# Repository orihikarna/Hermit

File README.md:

# Hermit - An Ergonomic Narrow-Pitch Split Keyboard

</img>

## Introduction
This is a personal hobby project on DIY keyboard.
The name *Hermit* comes from its key switch layout: it looked like a hermit crab.

Before working on this "full" keyboard, I made a test split keypad with 10 keys as a proof of concept model, which was named *Zoea*.

</img>

### Features
- Symmetric split with 60 keys
  - Key switch: Choc V2
  - Narrow pitch: 17.4 x 16.8mm
  - Thumb keys placed a bit further (to press them with the first joint)
  - Full color RGB LED
- Controller
  - ARM (STM32F042K6T6)
  - I/O expander (MCP23017) via I2C (using USB Type-C cable)
  - Debounce RC circuit (firmware reads Col 1ms after writing Row)
- Firmware
  - C++ bare-metal (STM32CubeIDE)
  - Stream processing with FIFO's (no immediate sending of key presses/releases)
  - Emacs translation (ex. `C-d` -> `Del`)

## Key switch layout
Before assembling ErgoDash, I really liked the key touch of Realforce and had used it for a decade.
However, once I got used to ErgoDash, I could not go back to Realforce anymore because `B` key was too far for my left index finger.
In fact, I started feeling pain in the index finger after typing on Realforce for a day.

One day, I came across [Treadstone](https://booth.pm/ja/items/1434972) layout, where the `B` key, or the left half of the bottom row, is shifted to the left a bit.
I thought this is the answer for me and I should follow this design.

### Cardboard prototyping
To begin with, I placed keycaps on a cardboard with lines of double sided tapes on it, and try tapping on it.
Sometimes added more keys, and other times removed some of them to find one that suits my fingers.

</img>

### 3D printer prototyping
After I purchased a 3D printer, I continued the seek for the layout using the actual Choc V2 key switches on 3D printed frames.
It enabled me to more finely adjust:
- Number of keys
- Key pitch: 17.0 ~ 18.0mm
- Key column positions and angles, especially for the thumbs

I usually use Japanese key layouts, and I found that 60 keys is the minimum that I can accept.
I wanted to keep most of the symbol keys on the board (without layers).

</img>

### Parametric model
When the layout was roughly determined, I tried to parametrize the layout to adjust the degree of ergonomic-ness.
The strategies are:
- Ring finger keys are on a straight line
- `B` is a bit on the left of `G`
- Pinky finger keys are lower than ring finger keys
- Keys are tightly touching to each other

And finally settled down on the current layout.

</img>

## PCB Design
This keyboard is composed of 6 PCB layers and is 8mm thick in total.
- Top layer (1.6mm)
- Second top layer (0.8mm)
- Circuit layer (1.6mm, Left and Right)
- Mid layer (1.2mm x2)
- Bottom layer (1.6mm)

</img>

I used KiCad v5.1.5 for the PCB design.

### Top
- Supports key switches.
- Common to Left and Right (reversible).

</img>

### Second top
- Fills in the gap between the top plate and the bottom of the box part of the key switches.
- Gives holes for USB connecter terminals.
- Common to Left and Right.

</img>

#### Circuit Left & Right
- Implements the circuitry, and USB connecters.

</img>
</img>

#### Middle
- Fills in the gap between the bottom plate and the bottom of the axis part of the key switches.
- USB connecter island will be removed for Left.

</img>

#### Bottom
- Common to Left and Right.

</img>

### Place & route by Python script
All the footprint placement, wire routing, vias, silkscreen labels, Edge.Cuts and GND zones are done by a Python script.

Currently, only the component side (Front or Back) needs to be set manually first.
Then, from `Script Console` of Pcbnew layout editor, run
```
exec(open('/(your path)/Hermit/python/place-route-Hermit.py').read())
```
and everything will be done in seconds!
(Although it took 2 month for me to write the script, of course!)

For example, in the script, the wire from C21 (debounce capacitor) pad 1 to U1 (main mcu) pad 29 is written as:
```
            ('C21', '1', 'U1', '29', w_mcu, (Dird, 90, ([(5.8, 90)], 0), r_col)),
```
This means that:
- the wire width is w_mcu
- from C21 pad 1, extend wire in the direction of 90deg
- from U1 pad 29, draw a wire for 5.8mm in the 90deg direction, and then, extend it to the direction of 0deg
- the intersection of the two lines will automatically be found
- make corners round by radius r_col

</img>

This way, the wiring is parallel to each part and looks roundy at corners.

## Debounce RC circuit
The mechanical key switches chatter sometimes.
Most DIY keyboards use software debouncing technique that comes with qmk (the standard keyboard firmware), where the key state (pressed or not) is examined twice with several milliseconds interval.
So, the switch bounce is hidden usually.
However, for the last two years, I experienced a couple of keys of my ErgoDash exhibited the chattering only in a specific season, i.e., in July or August in Japan.
I guess the software debounce might not be enough when it is very hot and super humid.
I've therefore added debounce RC for each column lines:

</img>

- When a key switch is released,
  - the Col lines are pulled down to GND.
  - the capacitors are fully charged.
- When a key switch is pressed,
  - the Row lines discharge the capacitors through key matrix diodes.
  - the Col lines rise to 5.0V or 3.3V minus 0.7V of the diode drop
- The time constant is different for discharging and charging, but they are set to about 1ms.
- Firmware needs to wait for 1~2ms before reading Col lines after writing Row lines.

I will check if this will actually contribute to reduce the switch bounce in the next summer!

For more information on hardware debounce, please refer to articles such as
[Ultimate Guide to Switch Debounce (Part 3)](https://www.eejournal.com/article/ultimate-guide-to-switch-debounce-part-3/)

## Rectangular holes for hexagon spacers
In Zoea PCB, it was useful to use hexagonal hole for spacers to keep them fixed: they won't rotate when tightening screws from the top and the bottom plates.
However, I needed to carefully choose the hexagon radius and the radius of the hexagon corners taking into account the endmill diameter.
So, this time, I used rectangular holes for the same purpose. I didn't have to consider much about the radius of the rectangle corners because any value would be fine with hexagon.

</img>

## Boundary avoidance using distance transform
I wanted to fill the surface of the top and the bottom plates with some design other than just nothing.
I'm not an artsy person at all, so I decided to draw simple stripes on them that curve along with the key switch angles.
The problem was that, how to end the stripe lines at the boundary of the board, screw holes, and of course the key switch holes. I didn't want that to happen all of a sudden abruptly.

So, I figured out a way to end lines just before the boundaries:
1. Export Edge.Cuts to svg (KiCad)
1. Rasterize svg to png (cairosvg Python package)
1. Binarize png to a mask image
1. Find connected components in the mask (OpenCV)
1. Choose the PCB component
1. Set initial distance (inside PCB = infinity, outside = 0)
1. Execute distance transform (OpenCV)

Then, you will get the distance from the boundaries.
It would be easier to end lines nicely at the boundaries: if it is near the boundary, you can use the distance value to find where to end the line.

The following figures are from Zoea top layer. First, the distance transform.

</img>

The final stripes on PCB. The thickness is reversed on its front and back.

</img>

It looked ok that time, however, I wanted to get closer to the edge this time...
So, divided thick lines into a multiple of thin lines:

</img>

and then, drew vertical / slant lines that connect the ends of thin horizontal lines:

</img>

## Firmware
For my studying of embedded programming, I wrote the firmware from scratch instead of using qmk.

### Stream processing
One thing I was thinking about qmk was register_code() and unregister_code() functions: these are used everywhere to send keycodes in the chain of processing.
However, since they send keycodes immediately, there is no room to to do more processing on the processed keycodes in the middle of the chain.

Of course, there are pros and cons.
But I wanted to try a stream structure, where each keycode processor is connected with FIFOs one after another to allow for successive processing.
Also, only one HID report will be prepared in the big loop that runs every 2ms.

A difficult part is the estimation of the required size for each FIFO.
If the FIFO size is too short, a processor in the chain cannot output anything and the entire stream would get stuck.

### Full Color RGB LED
At first, I placed LC8822-2020 on the key switch side of PCB.
They are good since they have separate data and clock lines (total 6 lines).
However, I noticed later that when they got broken, it is difficult to replace them because key switches are soldered above them.

Then, I decided to use SK6812-MINI-E, which is commonly used in DIY keyboards.
It has only one line for both data and clock, so it needs strict timing to send data.
There are 60 keys on Hermit, so that it takes 2ms to send series of data for all of them at once.
As 2ms felt too long, I split them to left and right half, and reduced the duration of interrupt-disabled periods to 1ms each.

</img>

### Emacs translation
I have been using Emacs key-binding for years.
There are ways to emulate it in a software manner on Windows, but what if it is inside a keyboard itself?

Although the current implementation needs tap & hold for single press of CTRL and ALT, other than that, it is working nicely!

### Minimizing the code size
At first, the code bloated with STM32 HAL USB library and printf (for debugging purpose) to more than 20KB.
However, thanks to STM32 LL library and the following libraries:
- [libusb_stm32](https://github.com/dmitrystu/libusb_stm32)
- [mini-printf](https://github.com/mludvig/mini-printf)

even after implemented RGB effects and Emacs translations, the current code size is:
- text: 16KB
- data+bss: 2.5KB

namely, only the half of STM32F042 capacity (32KB/6KB) is used.

## USB connector holders
For USB Type-C connectors, I gave up using the full 24-pin type due to the lack of my ability to solder them on PCB.
Instead, 16-pin type is used, where I2C is sent over D+/D- and LED signal is sent over SBU1/2.
Although other USB3.0 signal lines are not used at all, only because SBU1/2 is used, "full spec" Type-C cable is required to connect left and right.
They are thick in general and their stiffness gives strong forces on USB connectors.
So, I printed a simple-extrusion-work cable connector holder for them.
They need to be printed for each connector shape, but fit well and the cables are firmly attached to the keyboard.

</img>

## Finally, a short video
[Rainbow shaped Rainbow effect](https://twitter.com/orihikarna/status/1439446049446264836)

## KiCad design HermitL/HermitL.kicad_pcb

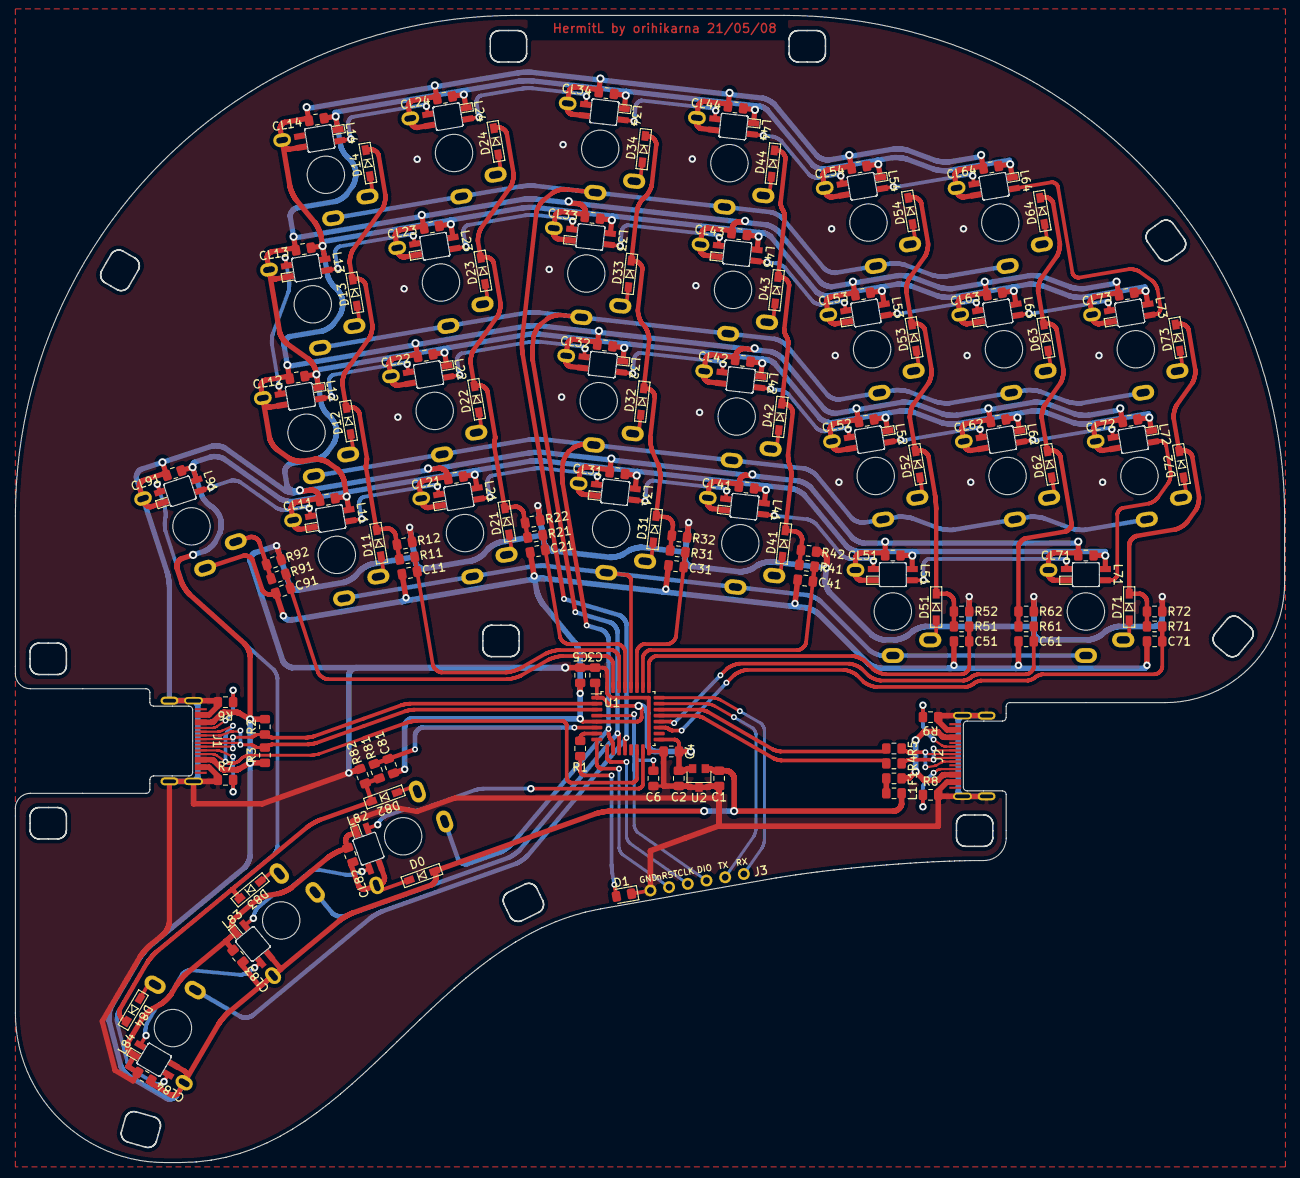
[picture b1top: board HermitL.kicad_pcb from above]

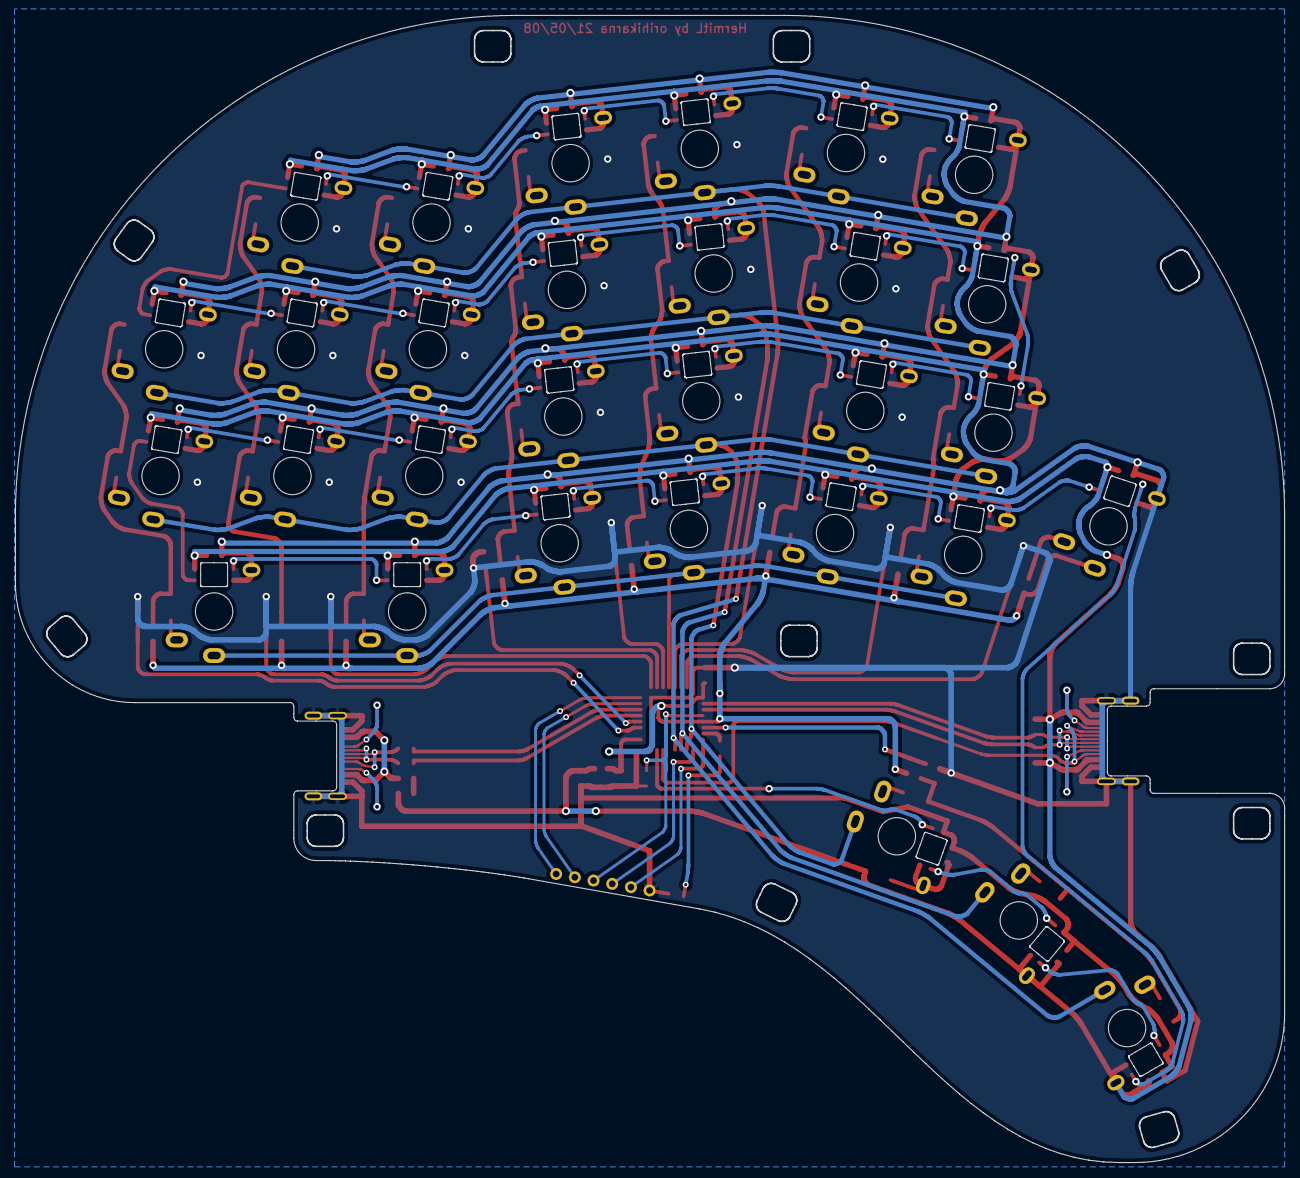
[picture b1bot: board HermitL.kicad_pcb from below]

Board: 2 copper layers, 169.9 x 153.6 mm, 170 parts (60 on the bottom side), 106 nets.

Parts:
C1: 1uF; C_0805_2012Metric_Pad1.15x1.40mm_HandSolder
C2: 10uF; C_0805_2012Metric_Pad1.15x1.40mm_HandSolder
C3, C4, C6: 0.1uF; C_0805_2012Metric_Pad1.15x1.40mm_HandSolder
C5: 4.7uF; C_0805_2012Metric_Pad1.15x1.40mm_HandSolder
C11, C21, C31, C41, C51, C61, C71, C81, C91: 33n; C_0805_2012Metric_Pad1.15x1.40mm_HandSolder
CL11, CL12, CL13, CL14, CL21, CL22, CL23, CL24, CL31, CL32, CL33, CL34, CL41, CL42, CL43, CL44, CL51, CL52, CL53, CL54, CL62, CL63, CL64, CL71, CL72, CL73, CL82, CL83, CL84, CL91: 0.1uF; C_0805_2012Metric_Pad1.15x1.40mm_HandSolder
D0, D11, D12, D13, D14, D21, D22, D23, D24, D31, D32, D33, D34, D41, D42, D43, D44, D51, D52, D53, D54, D62, D63, D64, D71, D72, D73, D82, D83, D84: D_Small; D_SMD
D1: LED; D_0805_2012Metric_Pad1.15x1.40mm_HandSolder
F1: Polyfuse; Fuse_0805_2012Metric_Pad1.15x1.40mm_HandSolder
J1, J2: USB_C_Receptacle_USB2.0; USB_C_Receptacle_Hirose_CX90M-16P
J3: Conn_01x06; PinHeader_1x06_P2.54mm_Vertical
L1: BLM21; L_0805_2012Metric_Pad1.15x1.40mm_HandSolder
L11, L12, L13, L14, L21, L22, L23, L24, L31, L32, L33, L34, L41, L42, L43, L44, L51, L52, L53, L54, L62, L63, L64, L71, L72, L73, L82, L83, L84, L91: SK6812-MINI-E
R1: 330; R_0805_2012Metric_Pad1.15x1.40mm_HandSolder
R2, R3: 2K2; R_0805_2012Metric_Pad1.15x1.40mm_HandSolder
R4, R5: 22; R_0805_2012Metric_Pad1.15x1.40mm_HandSolder
R6, R7, R8, R9: 5k1; R_0805_2012Metric_Pad1.15x1.40mm_HandSolder
R11, R21, R31, R41, R51, R61, R71, R81, R91: 10k; R_0805_2012Metric_Pad1.15x1.40mm_HandSolder
R12, R22, R32, R42, R52, R62, R72, R82, R92: 4k7; R_0805_2012Metric_Pad1.15x1.40mm_HandSolder
SW11, SW12, SW13, SW14, SW21, SW22, SW23, SW24, SW31, SW32, SW33, SW34, SW41, SW42, SW43, SW44, SW51, SW52, SW53, SW54, SW62, SW63, SW64, SW71, SW72, SW73, SW82, SW83, SW84, SW91: SW_ChocV2; ChocV2
U1: STM32F042K6Tx; LQFP-32_7x7mm_P0.8mm
U2: AP7333

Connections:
4V3: CL82.1, D0.1, L82.1, SW82.3
5V: C1.1, CL11.1, CL12.1, CL13.1, CL14.1, CL21.1, CL22.1, CL23.1, CL24.1, CL31.1, CL32.1, CL33.1, CL34.1, CL41.1, CL42.1, CL43.1, CL44.1, CL51.1, CL52.1, CL53.1, CL54.1, CL62.1, CL63.1, CL64.1, CL71.1, CL72.1, CL73.1, CL83.1, CL84.1, CL91.1, D0.2, J1.A4, J1.B4, L1.1, L11.1, L12.1, L13.1, L14.1, L21.1, L22.1, L23.1, L24.1, L31.1, L32.1, L33.1, L34.1, L41.1, L42.1, L43.1, L44.1, L51.1, L52.1, L53.1, L54.1, L62.1, L63.1, L64.1, L71.1, L72.1, L73.1, L83.1, L84.1, L91.1, R2.2, R3.2, SW12.3, SW14.3, SW22.3, SW24.3, SW32.3, SW34.3, SW42.3, SW44.3, SW52.3, SW54.3, SW62.3, SW64.3, SW72.3, SW83.3, SW84.3, U2.1
BOOT0: C91.1, R91.1, U1.31
COL1: C11.1, R11.1, U1.30
COL2: C21.1, R21.1, U1.29
COL3: C31.1, R31.1, U1.27
COL4: C41.1, R41.1, U1.26
COL5: C51.1, R51.1, U1.25
COL6: C61.1, R61.1, U1.20
COL7: C71.1, R71.1, U1.19
COL8: C81.1, R81.1, U1.6
DM: R4.2, U1.21
DP: R5.2, U1.22
GND: C1.2, C2.2, C3.2, C4.2, C5.2, C6.2, D1.1, J1.A1, J1.B1, J1.S1, J1.S2, J1.S3, J1.S4, J2.A1, J2.B1, J2.S1, J2.S2, J2.S3, J2.S4, J3.1, R6.2, R7.2, R8.2, R9.2, R12.1, R22.1, R32.1, R42.1, R52.1, R62.1, R72.1, R82.1, R92.1, U1.16, U1.32, U2.3
GNDD: CL11.2, CL12.2, CL13.2, CL14.2, CL21.2, CL22.2, CL23.2, CL24.2, CL31.2, CL32.2, CL33.2, CL34.2, CL41.2, CL42.2, CL43.2, CL44.2, CL51.2, CL52.2, CL53.2, CL54.2, CL62.2, CL63.2, CL64.2, CL71.2, CL72.2, CL73.2, CL82.2, CL83.2, CL84.2, CL91.2, L11.3, L12.3, L13.3, L14.3, L21.3, L22.3, L23.3, L24.3, L31.3, L32.3, L33.3, L34.3, L41.3, L42.3, L43.3, L44.3, L51.3, L52.3, L53.3, L54.3, L62.3, L63.3, L64.3, L71.3, L72.3, L73.3, L82.3, L83.3, L84.3, L91.3, SW11.3, SW13.3, SW21.3, SW23.3, SW31.3, SW33.3, SW41.3, SW43.3, SW51.3, SW53.3, SW63.3, SW71.3, SW73.3, SW91.3
LDI: L82.4, U1.15
LED: R1.1, U1.7
NRST: C6.1, J3.4, U1.4
unnamed: D1.2, R1.2
unnamed: D11.1, D12.1, D13.1, D14.1, R11.2, R12.2
unnamed: D11.2, SW11.2
unnamed: D12.2, SW12.2
unnamed: D13.2, SW13.2
unnamed: D14.2, SW14.2
unnamed: D21.1, D22.1, D23.1, D24.1, R21.2, R22.2
unnamed: D21.2, SW21.2
unnamed: D22.2, SW22.2
unnamed: D23.2, SW23.2
unnamed: D24.2, SW24.2
unnamed: D31.1, D32.1, D33.1, D34.1, R31.2, R32.2
unnamed: D31.2, SW31.2
unnamed: D32.2, SW32.2
unnamed: D33.2, SW33.2
unnamed: D34.2, SW34.2
unnamed: D41.1, D42.1, D43.1, D44.1, R41.2, R42.2
unnamed: D41.2, SW41.2
unnamed: D42.2, SW42.2
unnamed: D43.2, SW43.2
unnamed: D44.2, SW44.2
unnamed: D51.1, D52.1, D53.1, D54.1, R51.2, R52.2
unnamed: D51.2, SW51.2
unnamed: D52.2, SW52.2
unnamed: D53.2, SW53.2
unnamed: D54.2, SW54.2
unnamed: D62.1, D63.1, D64.1, R61.2, R62.2
unnamed: D62.2, SW62.2
unnamed: D63.2, SW63.2
unnamed: D64.2, SW64.2
unnamed: D71.1, D72.1, D73.1, R71.2, R72.2
unnamed: D71.2, SW71.2
unnamed: D72.2, SW72.2
unnamed: D73.2, SW73.2
unnamed: D82.1, D83.1, D84.1, R81.2, R82.2
unnamed: D82.2, SW82.2
unnamed: D83.2, SW83.2
unnamed: D84.2, SW84.2
unnamed: F1.2, L1.2
unnamed: J1.A5, R6.1
unnamed: J1.B5, R7.1
unnamed: J2.A5, R8.1
unnamed: J2.A6, J2.B6, R5.1
unnamed: J2.A7, J2.B7, R4.1
unnamed: J2.B5, R9.1
unnamed: L11.2, L21.4
unnamed: L11.4, L91.2
unnamed: L12.2, L13.4
unnamed: L12.4, L22.2
unnamed: L13.2, L23.4
unnamed: L14.4, L24.2
unnamed: L21.2, L31.4
unnamed: L22.4, L32.2
unnamed: L23.2, L33.4
unnamed: L24.4, L34.2
unnamed: L31.2, L41.4
unnamed: L32.4, L42.2
unnamed: L33.2, L43.4
unnamed: L34.4, L44.2
unnamed: L41.2, L51.4
unnamed: L42.4, L52.2
unnamed: L43.2, L53.4
unnamed: L44.4, L54.2
unnamed: L51.2, L71.4
unnamed: L52.4, L62.2
unnamed: L53.2, L63.4
unnamed: L54.4, L64.2
unnamed: L62.4, L72.2
unnamed: L63.2, L73.4
unnamed: L64.4, L73.2
unnamed: L71.2, L72.4
unnamed: L82.2, L83.4
unnamed: L83.2, L84.4
unnamed: L84.2, L91.4
unnamed: R91.2, R92.2, SW91.2
RDI: J1.A8, J1.B8, U1.14
ROW1: SW11.1, SW21.1, SW31.1, SW41.1, SW51.1, SW71.1, U1.28
ROW2: SW12.1, SW22.1, SW32.1, SW42.1, SW52.1, SW62.1, SW72.1, SW82.1, U1.10
ROW3: SW13.1, SW23.1, SW33.1, SW43.1, SW53.1, SW63.1, SW73.1, SW83.1, U1.11
ROW4: SW14.1, SW24.1, SW34.1, SW44.1, SW54.1, SW64.1, SW84.1, U1.12
RX: J3.3, U1.9
SCL: J1.A6, J1.B6, R3.1, U1.3
SDA: J1.A7, J1.B7, R2.1, U1.2
SWCLK: J3.6, U1.24
SWDIO: J3.5, U1.23
TX: J3.2, U1.8
VBUS: F1.1, J2.A4, J2.B4
VCC: C2.1, C3.1, C4.1, C5.1, C11.2, C21.2, C31.2, C41.2, C51.2, C61.2, C71.2, C81.2, C91.2, SW91.1, U1.1, U1.5, U1.17, U2.2

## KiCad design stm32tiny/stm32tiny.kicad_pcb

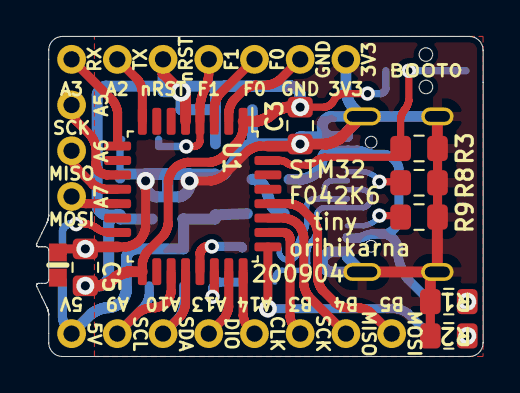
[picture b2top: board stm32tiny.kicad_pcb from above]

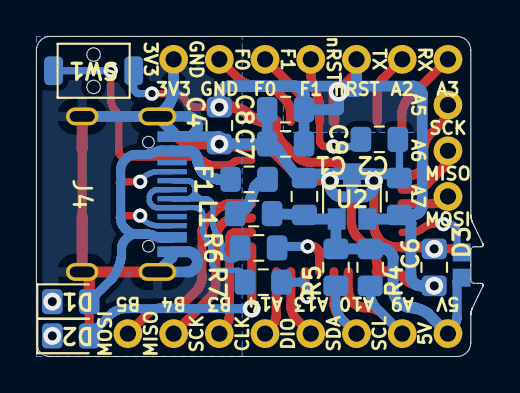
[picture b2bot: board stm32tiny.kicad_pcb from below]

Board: 2 copper layers, 24.8 x 17.8 mm, 30 parts (19 on the bottom side), 31 nets.

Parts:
C1, C8: 1uF; C_0805_2012Metric_Pad1.15x1.40mm_HandSolder
C2: 10uF; C_0805_2012Metric_Pad1.15x1.40mm_HandSolder
C3, C5, C9: 0.1uF; C_0805_2012Metric_Pad1.15x1.40mm_HandSolder
C4, C6: 4.7uF; C_0805_2012Metric_Pad1.15x1.40mm_HandSolder
C7: 0.01uF; C_0805_2012Metric_Pad1.15x1.40mm_HandSolder
D1: PW_LED; D_0805_2012Metric_Pad1.15x1.40mm_HandSolder
D2: LED; D_0805_2012Metric_Pad1.15x1.40mm_HandSolder
D3: SK6812-2020; WS2812B_2020_Vertical
F1: Polyfuse; Fuse_0805_2012Metric_Pad1.15x1.40mm_HandSolder
J1: Conn_01x08; PinHeader_1x08_P2.54mm_Vertical
J2: Conn_01x07; PinHeader_1x07_P2.54mm_Vertical
J3: Conn_01x03; PinHeader_1x03_P2.54mm_Vertical
J4: USB_C_Receptacle_USB2.0; USB_C_Receptacle_Neltron_5077CR
L1: BLM21; L_0805_2012Metric_Pad1.15x1.40mm_HandSolder
R1: 1K5; R_0805_2012Metric_Pad1.15x1.40mm_HandSolder
R2: 330; R_0805_2012Metric_Pad1.15x1.40mm_HandSolder
R3: 10K; R_0805_2012Metric_Pad1.15x1.40mm_HandSolder
R4, R5: 2K2; R_0805_2012Metric_Pad1.15x1.40mm_HandSolder
R6, R7: 22; R_0805_2012Metric_Pad1.15x1.40mm_HandSolder
R8, R9: 5k1; R_0805_2012Metric_Pad1.15x1.40mm_HandSolder
SW1: SW_Push; SW_SMD_5x3
U1: STM32F042K6Tx; LQFP-32_7x7mm_P0.8mm
U2: AP7333

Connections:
5V: C1.1, D3.4, J1.1, L1.1, R4.2, R5.2, U2.1
BOOT0: R3.1, SW1.2, U1.31
GND: C1.2, C2.2, C3.2, C4.2, C5.2, C6.2, C7.2, C8.2, C9.2, D3.2, J2.7, J4.A1, J4.B1, J4.S1, J4.S2, J4.S3, J4.S4, R1.2, R2.2, R3.2, R8.2, R9.2, U1.16, U1.32, U2.3
NRST: C9.1, J2.4, U1.4
unnamed: D1.1, R1.1
unnamed: D2.1, R2.1
unnamed: F1.2, L1.2
unnamed: J4.A5, R8.1
unnamed: J4.A6, J4.B6, R7.1
unnamed: J4.A7, J4.B7, R6.1
unnamed: J4.B5, R9.1
unnamed: R6.2, U1.21
unnamed: R7.2, U1.22
PA2: J2.2, U1.8
PA3: J2.1, U1.9
PA5: J3.1, U1.11
PA6: J3.2, U1.12
PA7: J3.3, U1.13
PA9: J1.2, R4.1, U1.19
PA10: J1.3, R5.1, U1.20
PA13: J1.4, U1.23
PA14: J1.5, U1.24
PA15: D2.2, U1.25
PB1: D3.3, U1.15
PB3: J1.6, U1.26
PB4: J1.7, U1.27
PB5: J1.8, U1.28
PF0: J2.6, U1.2
PF1: J2.5, U1.3
VBUS: D1.2, F1.1, J4.A4, J4.B4
VCC: C2.1, C3.1, C4.1, C5.1, C6.1, C7.1, C8.1, J2.3, SW1.1, U1.1, U1.5, U1.17, U2.2

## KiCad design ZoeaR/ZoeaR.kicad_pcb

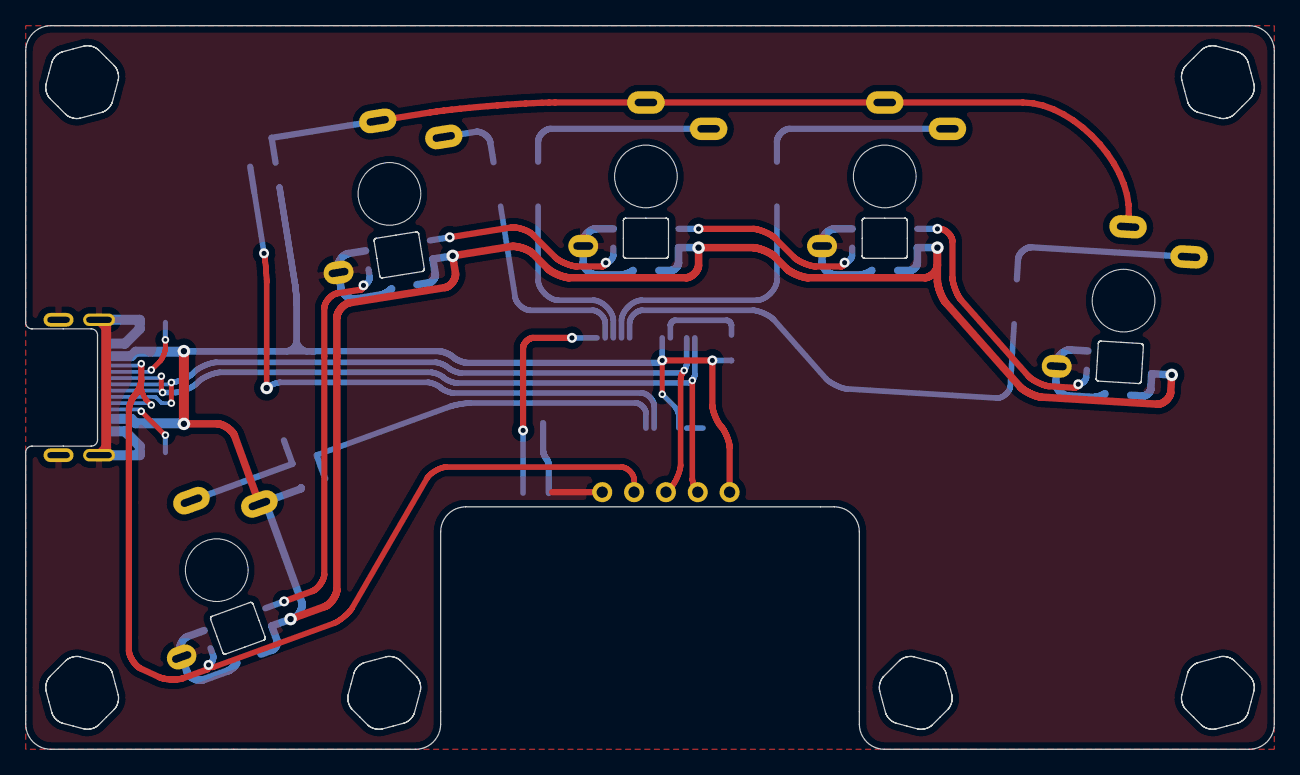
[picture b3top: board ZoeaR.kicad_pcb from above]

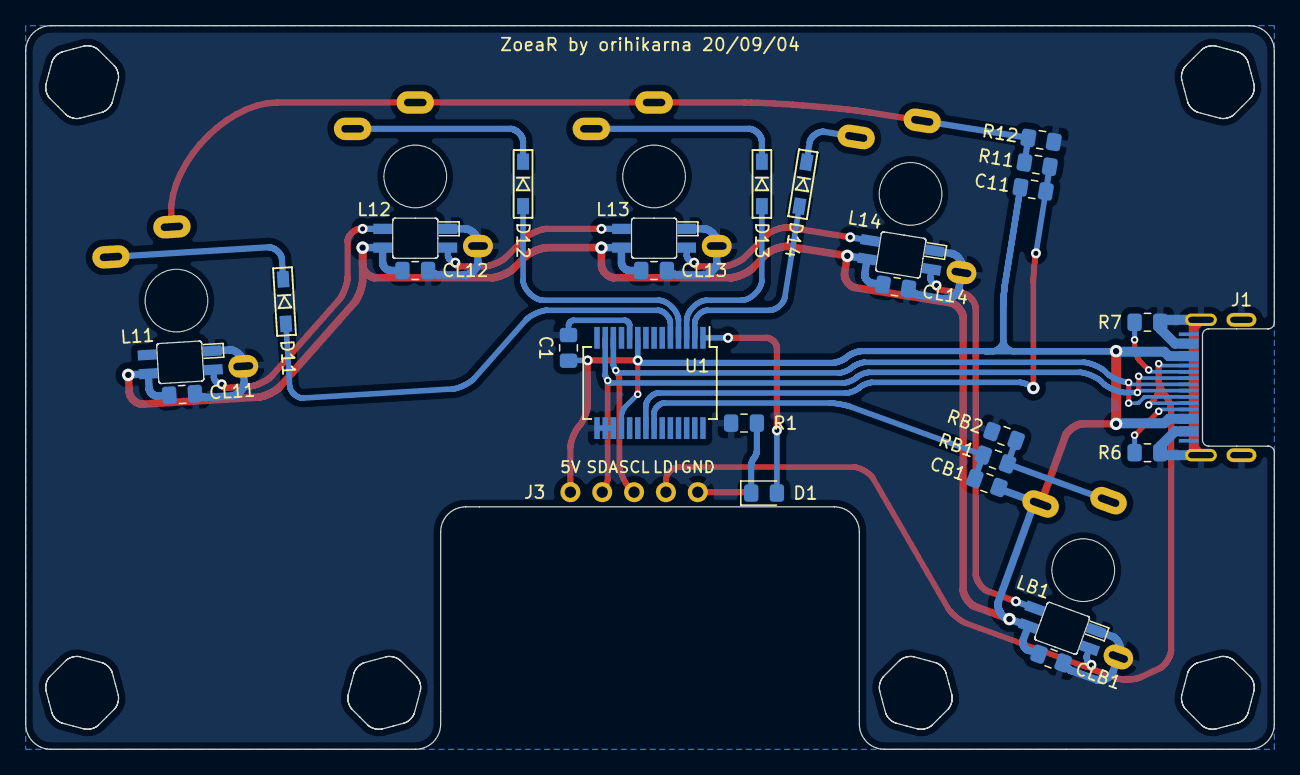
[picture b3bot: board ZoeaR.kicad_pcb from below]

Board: 2 copper layers, 99.6 x 57.7 mm, 33 parts (22 on the bottom side), 25 nets.

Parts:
C1: 0.1u; C_0805_2012Metric_Pad1.15x1.40mm_HandSolder
C11: 33n; C_0805_2012Metric_Pad1.15x1.40mm_HandSolder
CB1: 33n; C_0805_2012Metric_Pad1.15x1.40mm_HandSolder
CL11, CL12, CL13, CL14: 0.1u; C_0805_2012Metric_Pad1.15x1.40mm_HandSolder
CLB1: 0.1u; C_0805_2012Metric_Pad1.15x1.40mm_HandSolder
D1: LED; D_0805_2012Metric_Pad1.15x1.40mm_HandSolder
D11, D12, D13, D14: D_Small; D_SMD
J1: USB_C_Receptacle_USB2.0; USB_C_Receptacle_Hirose_CX90M-16P
J3: Conn_01x05; PinHeader_1x05_P2.54mm_Vertical
L11, L12, L13, L14: SK6812-MINI-E
LB1: SK6812-MINI-E
R1: 330; R_0805_2012Metric_Pad1.15x1.40mm_HandSolder
R6, R7: 5k1; R_0805_2012Metric_Pad1.15x1.40mm_HandSolder
R11: 10k; R_0805_2012Metric_Pad1.15x1.40mm_HandSolder
R12: 4k7; R_0805_2012Metric_Pad1.15x1.40mm_HandSolder
RB1: 10k; R_0805_2012Metric_Pad1.15x1.40mm_HandSolder
RB2: 4k7; R_0805_2012Metric_Pad1.15x1.40mm_HandSolder
SW11, SW12, SW13, SW14: SW_ChocV2; ChocV2
SWB1: SW_ChocV2; ChocV2
U1: MCP23017_SS; SSOP-28_5.3x10.2mm_P0.65mm

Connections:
5V: C1.1, C11.1, CB1.1, CL11.1, CL12.1, CL13.1, CL14.1, CLB1.1, J1.A4, J1.B4, J3.5, L11.1, L12.1, L13.1, L14.1, LB1.1, SWB1.2, U1.9, U1.18
BOOT0: CB1.2, RB1.2, U1.22
COL1: C11.2, R11.2, U1.21
GND: C1.2, CL11.2, CL12.2, CL13.2, CL14.2, CLB1.2, J1.A1, J1.B1, J1.S1, J1.S2, J1.S3, J1.S4, J3.1, L11.3, L12.3, L13.3, L14.3, LB1.3, R1.2, R6.2, R7.2, R12.2, RB2.2, SW11.3, SW12.3, SW13.3, SW14.3, SWB1.3, U1.10, U1.15, U1.16, U1.17
LDI: J1.A8, J1.B8, J3.2, LB1.4
LED: D1.2, U1.1
unnamed: D1.1, R1.1
unnamed: D11.1, SW11.2
unnamed: D12.1, SW12.2
unnamed: D13.1, SW13.2
unnamed: D14.1, SW14.2
unnamed: J1.A5, R6.1
unnamed: J1.B5, R7.1
unnamed: L11.4, L12.2
unnamed: L12.4, L13.2
unnamed: L13.4, L14.2
unnamed: L14.4, LB1.2
unnamed: R11.1, R12.1, SW11.1, SW12.1, SW13.1, SW14.1
unnamed: RB1.1, RB2.1, SWB1.1
ROW1: D11.2, U1.5
ROW2: D12.2, U1.4
ROW3: D13.2, U1.3
ROW4: D14.2, U1.2
SCL: J1.A6, J1.B6, J3.3, U1.12
SDA: J1.A7, J1.B7, J3.4, U1.13

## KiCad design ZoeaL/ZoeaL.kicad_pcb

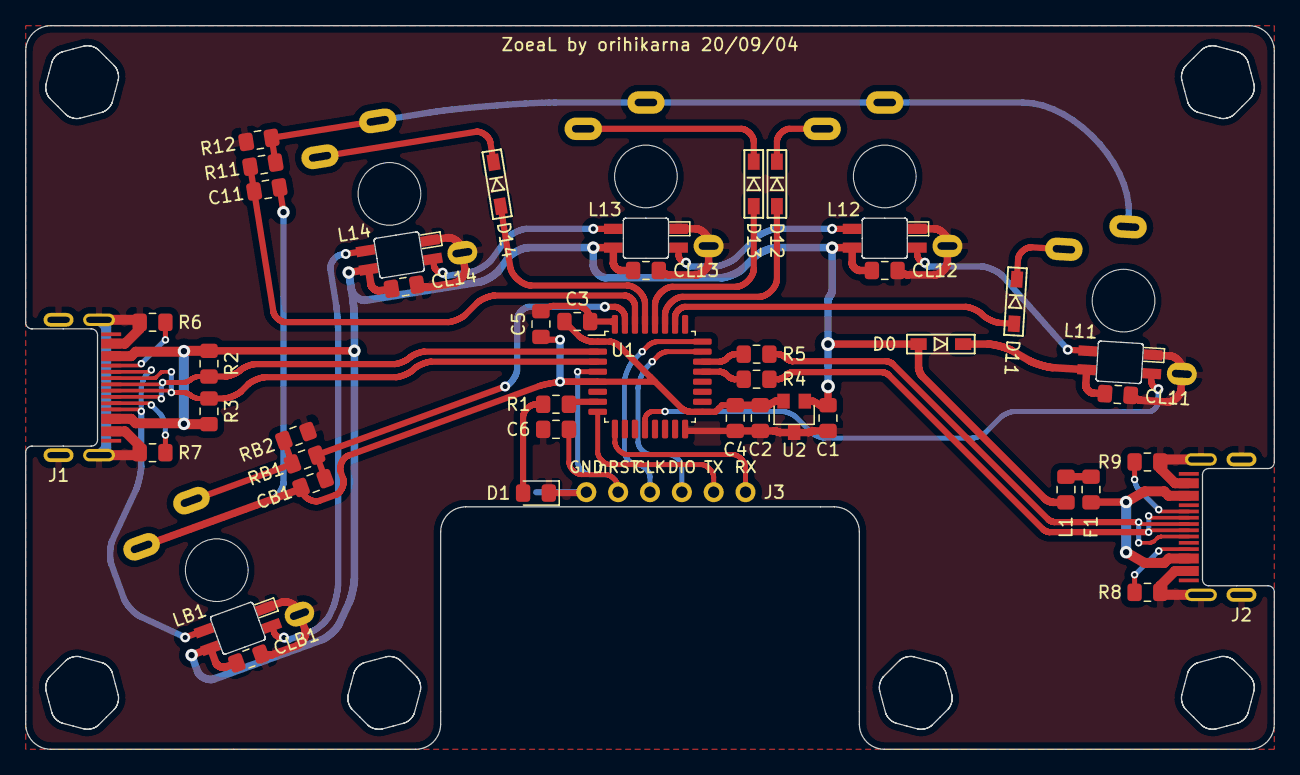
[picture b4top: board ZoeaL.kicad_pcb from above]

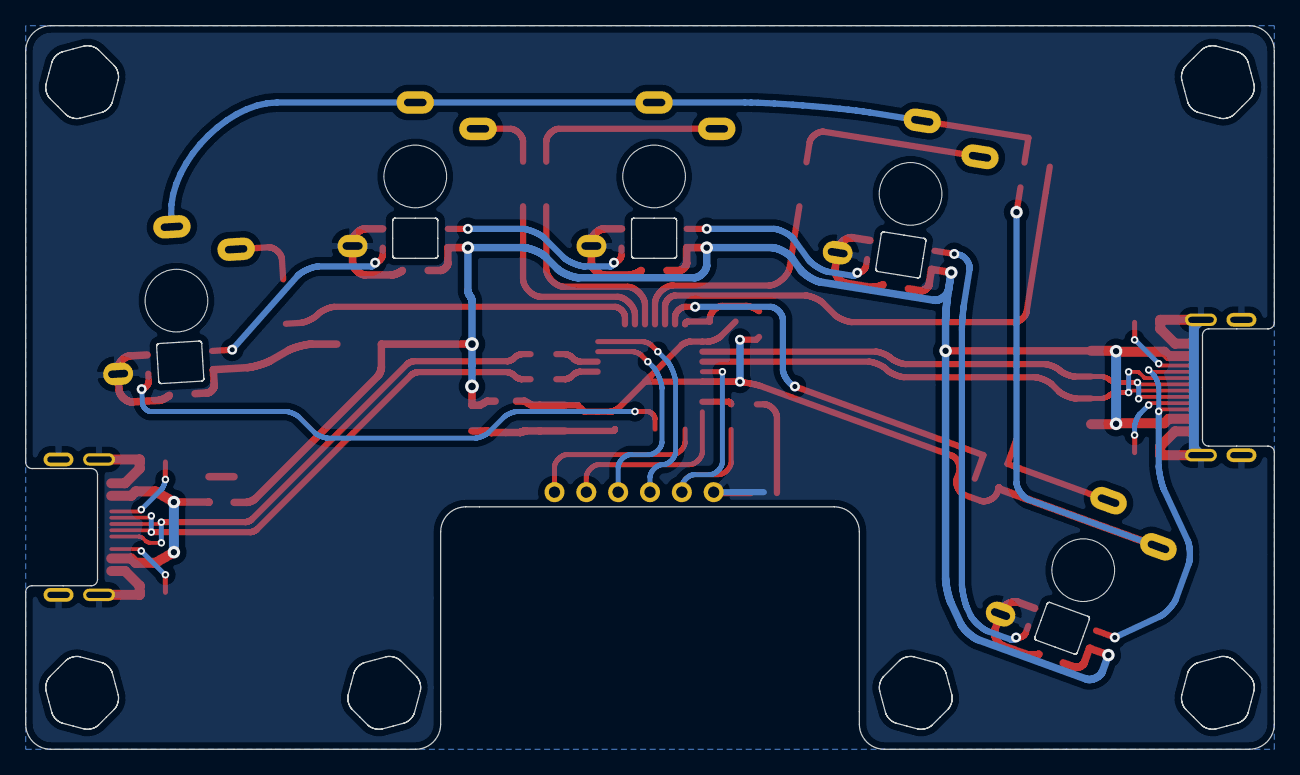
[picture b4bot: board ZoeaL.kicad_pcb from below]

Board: 2 copper layers, 99.6 x 57.7 mm, 49 parts (10 on the bottom side), 41 nets.

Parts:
C1: 1uF; C_0805_2012Metric_Pad1.15x1.40mm_HandSolder
C2: 10uF; C_0805_2012Metric_Pad1.15x1.40mm_HandSolder
C3, C4, C5, C6: 0.1uF; C_0805_2012Metric_Pad1.15x1.40mm_HandSolder
C11: 33n; C_0805_2012Metric_Pad1.15x1.40mm_HandSolder
CB1: 33n; C_0805_2012Metric_Pad1.15x1.40mm_HandSolder
CL11, CL12, CL13, CL14: 0.1uF; C_0805_2012Metric_Pad1.15x1.40mm_HandSolder
CLB1: 0.1uF; C_0805_2012Metric_Pad1.15x1.40mm_HandSolder
D0, D11, D12, D13, D14: D_Small; D_SMD
D1: LED; D_0805_2012Metric_Pad1.15x1.40mm_HandSolder
F1: Polyfuse; Fuse_0805_2012Metric_Pad1.15x1.40mm_HandSolder
J1, J2: USB_C_Receptacle_USB2.0; USB_C_Receptacle_Hirose_CX90M-16P
J3: Conn_01x06; PinHeader_1x06_P2.54mm_Vertical
L1: BLM21; L_0805_2012Metric_Pad1.15x1.40mm_HandSolder
L11, L12, L13, L14: SK6812-MINI-E
LB1: SK6812-MINI-E
R1: 330; R_0805_2012Metric_Pad1.15x1.40mm_HandSolder
R2, R3: 2K2; R_0805_2012Metric_Pad1.15x1.40mm_HandSolder
R4, R5: 22; R_0805_2012Metric_Pad1.15x1.40mm_HandSolder
R6, R7, R8, R9: 5k1; R_0805_2012Metric_Pad1.15x1.40mm_HandSolder
R11: 10k; R_0805_2012Metric_Pad1.15x1.40mm_HandSolder
R12: 4k7; R_0805_2012Metric_Pad1.15x1.40mm_HandSolder
RB1: 10k; R_0805_2012Metric_Pad1.15x1.40mm_HandSolder
RB2: 4k7; R_0805_2012Metric_Pad1.15x1.40mm_HandSolder
SW11, SW12, SW13, SW14: SW_ChocV2; ChocV2
SWB1: SW_ChocV2; ChocV2
U1: STM32F042K6Tx; LQFP-32_7x7mm_P0.8mm
U2: AP7333

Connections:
4V3: CL11.1, D0.1, L11.1
5V: C1.1, CL12.1, CL13.1, CL14.1, CLB1.1, D0.2, J1.A4, J1.B4, L1.1, L12.1, L13.1, L14.1, LB1.1, R2.2, R3.2, U2.1
BOOT0: CB1.2, RB1.2, U1.31
COL1: C11.2, R11.2, U1.30
GND: C1.2, C2.2, C3.2, C4.2, C5.2, C6.2, CL11.2, CL12.2, CL13.2, CL14.2, CLB1.2, D1.1, J1.A1, J1.B1, J1.S1, J1.S2, J1.S3, J1.S4, J2.A1, J2.B1, J2.S1, J2.S2, J2.S3, J2.S4, J3.1, L11.3, L12.3, L13.3, L14.3, LB1.3, R6.2, R7.2, R8.2, R9.2, R12.2, RB2.2, SW11.3, SW12.3, SW13.3, SW14.3, SWB1.3, U1.16, U1.32, U2.3
LDI: L11.4, U1.12
LDO: J1.A8, J1.B8, LB1.2
LED: R1.1, U1.7
NRST: C6.1, J3.2, U1.4
unnamed: D1.2, R1.2
unnamed: D11.1, SW11.2
unnamed: D12.1, SW12.2
unnamed: D13.1, SW13.2
unnamed: D14.1, SW14.2
unnamed: F1.2, L1.2
unnamed: J1.A5, R6.1
unnamed: J1.B5, R7.1
unnamed: J2.A5, R8.1
unnamed: J2.A6, J2.B6, R5.1
unnamed: J2.A7, J2.B7, R4.1
unnamed: J2.B5, R9.1
unnamed: L11.2, L12.4
unnamed: L12.2, L13.4
unnamed: L13.2, L14.4
unnamed: L14.2, LB1.4
unnamed: R4.2, U1.21
unnamed: R5.2, U1.22
unnamed: R11.1, R12.1, SW11.1, SW12.1, SW13.1, SW14.1
unnamed: RB1.1, RB2.1, SWB1.1
ROW1: D11.2, U1.26
ROW2: D12.2, U1.27
ROW3: D13.2, U1.28
ROW4: D14.2, U1.29
RX: J3.6, U1.9
SCL: J1.A6, J1.B6, R3.1, U1.3
SDA: J1.A7, J1.B7, R2.1, U1.2
SWCLK: J3.3, U1.24
SWDIO: J3.4, U1.23
TX: J3.5, U1.8
VBUS: F1.1, J2.A4, J2.B4
VCC: C2.1, C3.1, C4.1, C5.1, C11.1, CB1.1, SWB1.2, U1.1, U1.5, U1.17, U2.2

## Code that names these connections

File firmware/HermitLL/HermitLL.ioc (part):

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Mcu.UserName=STM32F042K6Tx
PA0.GPIO_Label=COL8
PA9.GPIOParameters=GPIO_Label
PA6.GPIO_Label=ROW4
PB0.GPIO_Label=RDI
PB6.GPIO_Label=COL2
RCC.SYSCLKSource=RCC_SYSCLKSOURCE_HSI48
PB5.GPIOParameters=GPIO_Label
PA15.GPIO_Label=COL5
PB4.GPIOParameters=GPIO_Label
PB6.Signal=GPIO_Input
PB0.GPIOParameters=GPIO_Speed,GPIO_Label
PA1.GPIOParameters=GPIO_Label
PB1.GPIO_Speed=GPIO_SPEED_FREQ_HIGH
PA14.Mode=Serial_Wire
PB1.GPIO_Label=LDI
PA10.GPIO_Label=COL6
PB3.GPIOParameters=GPIO_Label
PB7.Signal=GPIO_Input
PB6.GPIOParameters=GPIO_Label
PA0.Signal=GPIO_Input
PB7.GPIO_Label=COL1
Mcu.Package=LQFP32
PB1.Signal=S_TIM3_CH4
PA6.Signal=GPIO_Output
PA10.Signal=GPIO_Input
PA15.Signal=GPIO_Input
PA5.GPIOParameters=GPIO_Label
PB5.GPIO_Label=ROW1
PF1-OSC_OUT.Mode=I2C
PA4.GPIO_Label=ROW2
PF1-OSC_OUT.Signal=I2C1_SCL
PB4.Signal=GPIO_Input
PA3.Signal=USART2_RX
PB3.GPIO_Label=COL4
PA6.GPIOParameters=GPIO_Label
PB8.GPIOParameters=GPIO_Label
PA15.GPIOParameters=GPIO_Label
PA9.GPIO_Label=COL7
PB0.GPIO_Speed=GPIO_SPEED_FREQ_HIGH
PA13.Signal=SYS_SWDIO
PA3.Mode=Asynchronous
PB8.GPIO_Label=COLB
PB7.GPIOParameters=GPIO_Label
PA9.Signal=GPIO_Input
PA1.Signal=GPIO_Output
PF0-OSC_IN.Mode=I2C
PA5.Signal=GPIO_Output
board=custom
PB4.GPIO_Label=COL3
PA1.GPIO_Label=LED
PA10.GPIOParameters=GPIO_Label
PA4.GPIOParameters=GPIO_Label
PA13.Mode=Serial_Wire
Mcu.Name=STM32F042K(4-6)Tx
PA2.Signal=USART2_TX
PB3.Signal=GPIO_Input
PA4.Signal=GPIO_Output
RCC.SYSCLKFreq_VALUE=48000000
PB5.Signal=GPIO_Output
PA5.GPIO_Label=ROW3
PA14.Signal=SYS_SWCLK
PA0.GPIOParameters=GPIO_Label
PA2.Mode=Asynchronous
PB8.Signal=GPIO_Input
PF0-OSC_IN.Signal=I2C1_SDA
PB0.Signal=S_TIM3_CH3
PB1.GPIOParameters=GPIO_Speed,GPIO_Label

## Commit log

2020-06-02 added layouter
2020-06-02 both hand keys
2020-06-02 fixed thumb key angles
2020-06-02 path contatination
2020-06-02 removed yoffset params
2020-06-02 use deg2rad/rad2deg
2020-06-04 parameter animation, fixed png output
2020-06-09 finished schematics, placed parts
2020-06-09 added kad scripts
2020-06-11 more on wire_mods
2020-06-12 refactoring Dird2
2020-06-13 fixed zigzag
2020-06-13 refactored wire_mods
2020-06-13 multiple offsers
2020-06-14 done place & route roughly
2020-06-15 adjusted pcb size
2020-06-16 added more i/o
2020-06-17 added one more i/o, removed D3, moved D2
2020-06-18 D2 -> PA15, zigzag DM/DP, VBUS vias
2020-06-19 passed drc
2020-06-19 fixed the positions
2020-06-19 cleaning wire defs
2020-06-20 adjusted wires
2020-06-20 almost done wiring
2020-06-20 added references
2020-06-21 fusionpcb-200621
2020-06-21 plot gerber 200621
2020-06-30 added LED wall, modified USB footprint
2020-07-03 adjusting usb connector wiring
2020-07-05 relayouting
2020-07-05 Vcc zone, negative radius for Bezier wiring
2020-07-05 round wiring
2020-07-08 redid vias, round wire corners
2020-07-09 round wiring done
2020-07-10 adjusted references, wires
2020-07-12 triy adding brace keys on right
2020-07-23 modified braces key positions
2020-07-23 ignore gerber files
2020-07-31 created ZoecaRight projct
2020-08-02 renamed to ZoeaL
2020-08-03 started p&r
2020-08-07 roughly routed
2020-08-08 adjusting p&r
2020-08-09 drc, screw holes
2020-08-10 adjusted led pin
2020-08-12 hex holes
2020-08-13 created ZoeaR board
2020-08-15 started p&r right side
2020-08-15 added pass cap
2020-08-17 roughly done
2020-08-18 added top, mid, and bottom platex
2020-08-20 wiring angle
2020-08-21 working on mid plate
2020-08-22 making mid plate
2020-08-23 roughly done mid plate
2020-08-23 move references
2020-08-24 fixed right board
2020-08-27 top plate lines
2020-08-29 top plate pattern
2020-08-29 stm32tiny to migrate to new wiring
2020-08-30 cleaning ZoeaL
2020-08-30 cleaned ZoeaR
2020-08-30 improved top, bottom line drawing
2020-08-31 replacing LEDs
2020-09-01 added LED caps
2020-09-01 adjusted lb1 and l12
2020-09-02 redid right leds, moving diodes
2020-09-03 adjusted diode wiring
2020-09-03 replaced leds, added pass caps
2020-09-03 led wiring, debounce positions
2020-09-04 added j3 to right board
2020-09-04 200904 for submit
2020-09-05 changed mid plate holes to edge.cuts for jlcpcb issue
2020-11-30 modified layout
2020-12-03 scad output
2020-12-18 layout adjustments with 3D printer
2020-12-18 don't print keys for now
2020-12-23 layout adjustment
2020-12-24 adjusted pink bottom keys
2020-12-29 final key layout
2020-12-31 refactored code
2021-01-09 rectangular key size
2021-01-09 dump key_w, key_h to scad
2021-02-24 created HermitL
2021-02-24 print for kicad
2021-02-25 added Hermit place and router
2021-02-28 refactor scad output
2021-03-01 adjusted keys offset, pcb size
2021-03-01 changed switch and diode connections
2021-03-02 led ground, led placement
2021-03-03 led routing
2021-03-08 changed thumb key direction, routing led
2021-03-12 rename 81 to 84
2021-03-14 fixed SW71 connection
2021-03-15 rough routing
2021-03-16 adjusting led wires
2021-03-17 redid led wirings
2021-03-18 adjusted row lines, debounce RRCs
2021-03-19 adusted col lines
2021-03-21 adusted row, col wires
2021-03-21 layout animation
2021-03-27 redoing mcu vcc, gnd
2021-03-30 alpha for left side wiring
2021-03-30 initiated Right side
2021-04-01 ronting leds
2021-04-01 routing led, row, diodes
2021-04-02 wiring leds
2021-04-03 wiring row, col lines
2021-04-05 minor edit
2021-04-07 spline edge.cuts, adjusted angle
2021-04-15 refining wires, added mounting holes
2021-04-16 redid wiring for left & right
2021-04-24 draw edge cuts
2021-04-25 fixed wires, screw holes
2021-04-26 added all board projects
2021-05-01 added distance image for top plate
2021-05-02 bottom pattern
2021-05-03 refined wiring for L, refs for L
2021-05-04 refined BDR wiring
2021-05-05 reduced screws
2021-05-05 added png2bmp for stensil
2021-05-05 fixed distance image
2021-05-05 another layer
2021-05-05 refactor top & bottom lines
2021-05-05 fixing led pwr lines for L
2021-05-06 refined RGB power wires
2021-05-08 improved usb connector wiring
2021-05-08 changed logo date
2021-05-08 plot gerbers
2021-05-09 fixed keyswitch holes with Round option
2021-05-10 use bezier for future
2021-09-04 add firmware position output
2021-09-04 added radius and angle
2021-09-16 opt sw_pos table
2021-09-25 add symbols and footprints
2021-09-25 add Hermit firmware
2021-09-25 fixed paths
2021-09-26 updated readme.md with usb connector
2021-09-26 adjusted picture size
2021-09-26 adjusted image size
2021-09-26 updated a link
2021-12-04 right led on non-emacs mode
2022-03-18 fix paste code during marksel
